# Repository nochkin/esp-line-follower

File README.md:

# esp-line-follower
## Purpose
The goal of the project is to teach beginners into robotics without fearing and over-complicated or expensive parts.
It's indended to be open enough for future experiments and improvements.

## Required skills
* Basic soldering skills.
  A few wires need to be soldered here and there, nothing major.
* Some understanding on how electronic components are connected together
  Just enough to know the difference between "+" and "-", signal and power lines, etc.
* Basic knowledge on Arduino IDE and how sketches are uploaded.

## Required parts
This is the minimum list of required parts. Basically, these are the parts which are being used in this project.
The list should not limit you in case if you wish to add some additional functionality or make other experiments based on that.
* Microcontroller board.
  The project uses ESP8266 NodeMCU board with CP2102. Sometimes that board is referenced as "ESP8266 NodeMCU v2 DevKit".
  There are some variations of ESP8266 NodeMCU board with CH340G chip, but these are too wide to fit into motor driver shield and so can't be used.
* Motor driver shield.
  The shield is based on L293DD chip. A single chip contains four half-bridges which can be connected as two full bridges to drive two motors.
* A pair of Reflective Infrared sensor boards.
  These are sometimes called "Obstacles avoiding infrared sensor board". Each board contains an infrared LED and infrared photodiode.
  There are a lot of variations of those boards. I highly recommend to pick those with a small adjustment, this way it can be adjusted according to the current lighting and surrounding contrast.
* 2WD Robot Chassis.
  Normally, the chassis comes with two motors with built-in reductors, 4*AA battery holder and enough screws and mounting hardware to put everything together. You will still need some additional mounting/screws to put your ESP8266, Motor shield and Infrared sensors.

## Bill Of Materials (BOM)
All prices are approximate and depend on the source where you purchase it. My recommended sources are eBay and AliExpress. You can also find it on Amazon, but it tends to be slightly more expensive. All prices are in USD.

Qnty | Part | Cost | Buy
-- | - | - | -
1 | ESP8266 NodeMCU (CP2102) | $5.00 | [eBay](https://www.ebay.com/itm/201542946669), [AliExpress](https://www.aliexpress.com/item/32716698412.html), [Amazon](https://www.amazon.com/ESP8266-microcontroller-NodeMCU-WiFi-CP2102/dp/B071WRD25D/ref=sr_1_1?keywords=B071WRD25D&qid=1568748259&s=gateway&sr=8-1)
1 | L293DD Motor Shield for ESP8266 NodeMCU | $2.50 | [eBay](https://www.ebay.com/itm/400999618519), [AliExpress](https://www.aliexpress.com/item/32870926299.html), [Amazon](https://www.amazon.com/BeediY-NodeMCU-ESP-12E-ESP8266-Control/dp/B07QVCMM5B/ref=sr_1_1?keywords=B07QVCMM5B&qid=1568748516&s=gateway&sr=8-1)
2 | Infrared sensors | $1.50 | [eBay](https://www.ebay.com/itm/132461910910), [AliExpress](https://www.aliexpress.com/item/32757950384.html), [Amazon](https://www.amazon.com/HiLetgo-Infrared-Avoidance-Reflective-Photoelectric/dp/B07W97H2WS/ref=sr_1_1?keywords=B07W97H2WS&qid=1568748581&s=gateway&sr=8-1)
1 | 2WD Robot Chassis | $8.00 | [eBay](https://www.ebay.com/itm/253202993406), [AliExpress](https://www.aliexpress.com/item/32766175672.html), [Amazon](https://www.amazon.com/SainSmart-Smart-Chassis-Tracing-Encoder/dp/B07DNYQ3PX/ref=sr_1_1?keywords=B07DNYQ3PX&qid=1568748118&s=gateway&sr=8-1)
6 | 20cm Dupont Wires F-F to connect Infrared boards | $2.00 | [eBay](https://www.ebay.com/itm/283983743599)
1 | Various M3 spacers/standoffs/screws | $12.00 | [eBay](https://www.ebay.com/itm/173901459487), [AliExpress](https://www.aliexpress.com/item/32799855557.html), [Amazon](https://www.amazon.com/Yosoo-120pcs-standoff-motherboard-assortment/dp/B01GO2GWWW/ref=sr_1_1?keywords=B01GO2GWWW&qid=1569029665&sr=8-1)
1 | Black Cloth Tape, 32mm x 15m | $2.00 | [AliExpress](https://www.aliexpress.com/item/32964092687.html) |

**Total**: about $20

## Connection diagram

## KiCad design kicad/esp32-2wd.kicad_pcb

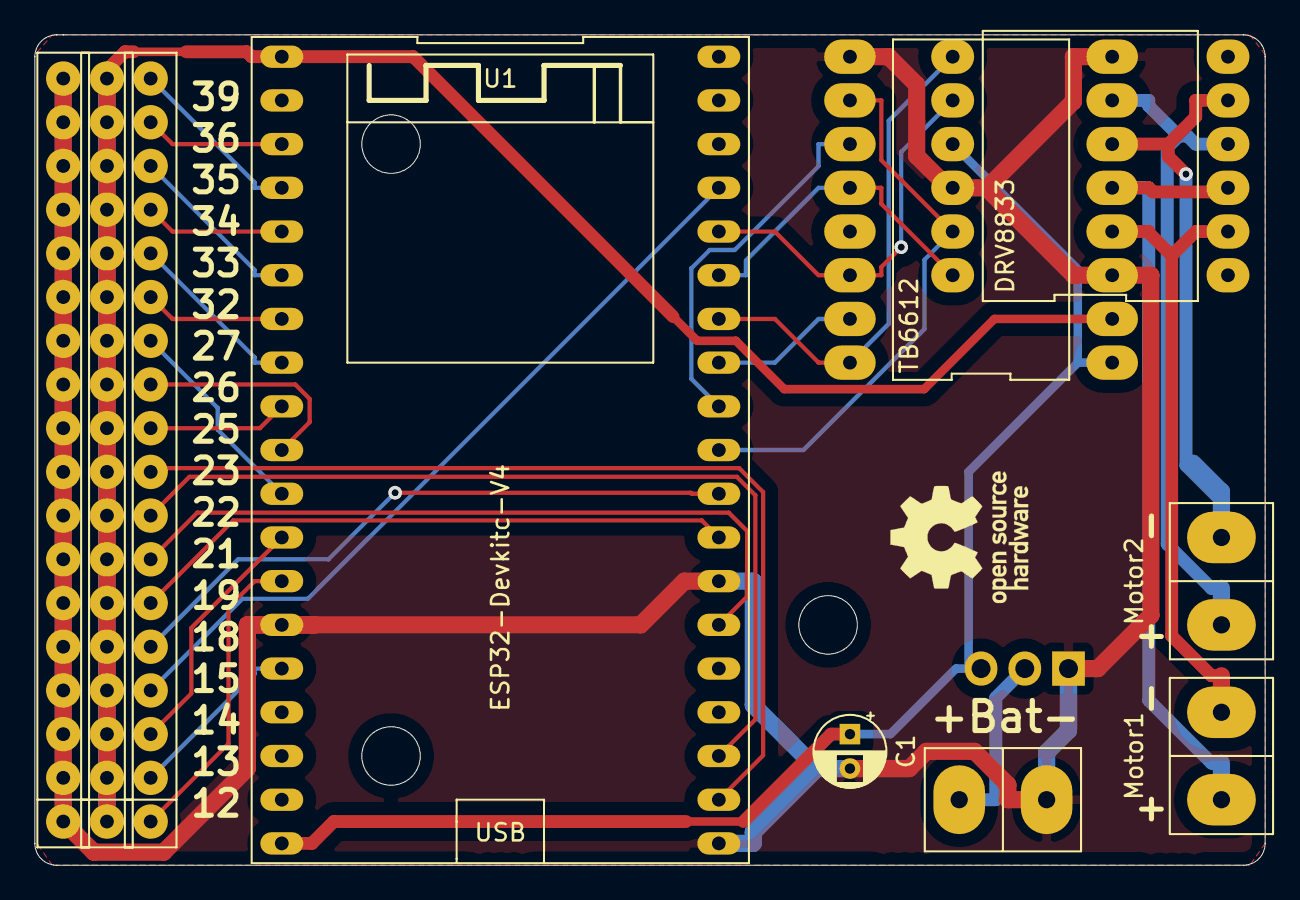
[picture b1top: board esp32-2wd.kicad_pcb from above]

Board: 2 copper layers, 71.5 x 48.3 mm, 11 parts (1 on the bottom side), 32 nets.

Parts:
Bat1: Screw_Conn_2p_508
C1: CP; CP_Radial_D4.0mm_P2.00mm
CONN1, CONN2, CONN3: Conn_1x18_254
DRV1: TB6612; TB6612-board
DRV2: DRV8833; DRV8833-12
Motor1, Motor2: Screw_Conn_2p_508
Q1: IRF9540N; TO-220-3_Vertical
U1: ESP32-Devkitc-V4; ESP32-DevKitC-V4-b

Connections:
GNDD: Bat1.1, C1.2, CONN1.1, CONN1.2, CONN1.3, CONN1.4, CONN1.5, CONN1.6, CONN1.7, CONN1.8, CONN1.9, CONN1.10, CONN1.11, CONN1.12, CONN1.13, CONN1.14, CONN1.15, CONN1.16, CONN1.17, CONN1.18, DRV1.3, DRV1.8, DRV1.9, DRV2.10, Q1.1, U1.14, U1.20, U1.26
unnamed: Bat1.2, Q1.2
unnamed: C1.1, DRV1.1, DRV2.9, Q1.3, U1.19
unnamed: CONN2.1, CONN2.2, CONN2.3, CONN2.4, CONN2.5, CONN2.6, CONN2.7, CONN2.8, CONN2.9, CONN2.10, CONN2.11, CONN2.12, CONN2.13, CONN2.14, CONN2.15, CONN2.16, CONN2.17, CONN2.18, DRV1.2, U1.1
unnamed: CONN3.1, U1.13
unnamed: CONN3.2, U1.15
unnamed: CONN3.3, U1.12
unnamed: CONN3.4, U1.35
unnamed: CONN3.5, U1.28
unnamed: CONN3.6, U1.27
unnamed: CONN3.7, U1.25
unnamed: CONN3.8, U1.22
unnamed: CONN3.9, U1.21
unnamed: CONN3.10, U1.9
unnamed: CONN3.11, U1.10
unnamed: CONN3.12, U1.11
unnamed: CONN3.13, U1.7
unnamed: CONN3.14, U1.8
unnamed: CONN3.15, U1.5
unnamed: CONN3.16, U1.6
unnamed: CONN3.17, U1.3
unnamed: CONN3.18, U1.4
unnamed: DRV1.4, DRV2.2, Motor1.2
unnamed: DRV1.5, DRV2.3, Motor1.1
unnamed: DRV1.6, DRV2.5, Motor2.2
unnamed: DRV1.7, DRV2.4, Motor2.1
unnamed: DRV1.10, DRV2.11, U1.29
unnamed: DRV1.11, U1.30
unnamed: DRV1.12, DRV2.12, U1.33
unnamed: DRV1.14, DRV2.8, U1.34
unnamed: DRV1.15, U1.31
unnamed: DRV1.16, DRV2.7, U1.32

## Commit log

2019-07-21 Sample Arduino code/library
2019-07-24 Add line following logic
2019-07-24 Minor cleanup
2019-07-29 Swap left/right motor logic
2019-08-19 Added overall connection diagram
2019-09-16 Add introduction and list of parts
2019-09-17 Add some Amazon links to BOM
2019-09-21 Added eBay and AliExpress links
2019-09-21 Fixed some links and formatting
2019-09-25 Added missing item to BOM
2020-11-10 Update external links
2021-08-24 Add connections.txt
2021-09-10 ESP32 compatibility
2021-09-24 Add KiCad files for ESP32 board
2021-09-24 Add KiCad's custom lib for ESP32 schematic
2022-08-13 TB6612 support
2022-08-16 Revert "TB6612 support"
    This reverts commit 02e79df51a6babfc2041ab42208772d88f71af53.
2022-08-16 Fix TB6612 support (ESP32 only) and compatibility fixes for ESP8266
2022-08-16 Support Enable pin for motor driver, add 1 sec delay before start
2022-08-16 Fix minor typo
2022-08-19 Use ledc instead of pwm for ESP32
2023-08-20 Add platformio.ini and move source to 'src'
2023-08-20 Add 'Started' serial output to make sure the code started
